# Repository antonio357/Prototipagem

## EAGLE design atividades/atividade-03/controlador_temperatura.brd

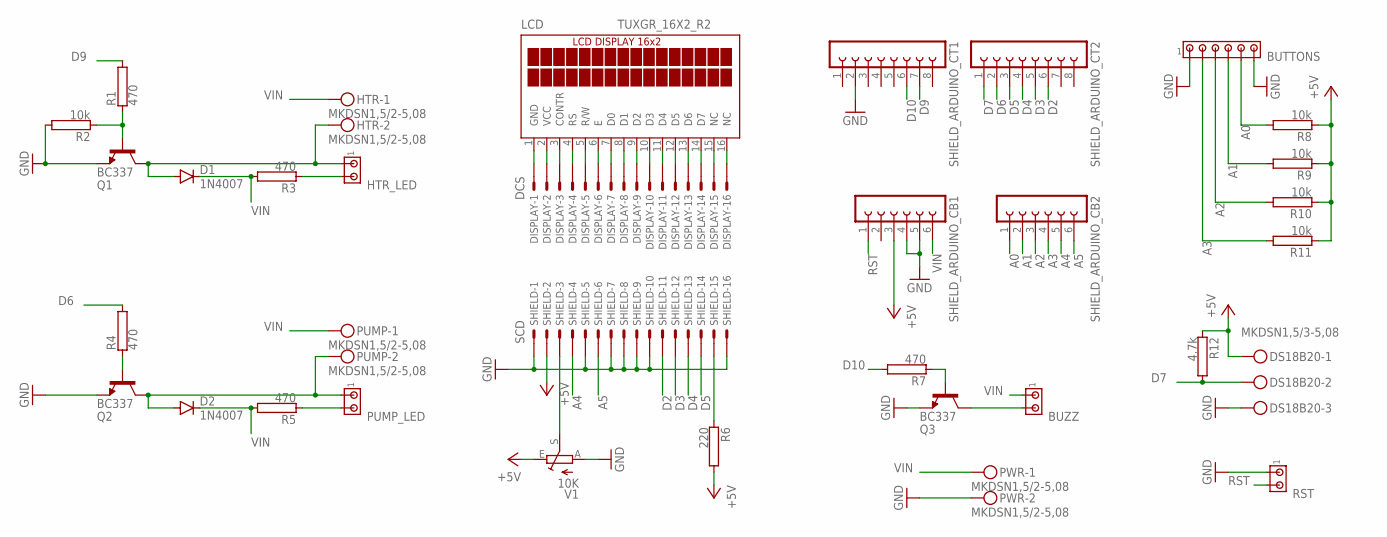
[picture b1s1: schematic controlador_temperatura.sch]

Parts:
BUTTONS: MTA06-100; 10X06MTA
BUZZ: MTA02-100; 10X02MTA
D1, D2: 1N4007; DO41-10
DISPLAY: DCS; 057-016-1
DS18B20: MKDSN1,5/3-5,08
HTR: MKDSN1,5/2-5,08
HTR_LED: MTA02-100; 10X02MTA
LCD: TUXGR_16X2_R2
PUMP: MKDSN1,5/2-5,08
PUMP_LED: MTA02-100; 10X02MTA
PWR: MKDSN1,5/2-5,08
Q1, Q2, Q3: BC337; TO92
R1, R3, R4, R5, R7: 470; RS1/8
R2, R8, R9, R10, R11: 10k; RS1/8
R6: 220; RS1/8
R12: 4.7k; RS1/8
RST: MTA02-100; 10X02MTA
SHIELD: SCD; 057-016-1
SHIELD_ARDUINO_CB1, SHIELD_ARDUINO_CB2: FE06-1; FE06
SHIELD_ARDUINO_CT1, SHIELD_ARDUINO_CT2: FE08-1; FE08
V1: 10K; B25P

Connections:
A0: BUTTONS.5, R8.2, SHIELD_ARDUINO_CB2.1
A1: BUTTONS.4, R9.2, SHIELD_ARDUINO_CB2.2
A2: BUTTONS.3, R10.2, SHIELD_ARDUINO_CB2.3
A3: BUTTONS.2, R11.2, SHIELD_ARDUINO_CB2.4
A4: SHIELD.4, SHIELD_ARDUINO_CB2.5
A5: SHIELD.6, SHIELD_ARDUINO_CB2.6
D2: SHIELD.11, SHIELD_ARDUINO_CT2.6
D3: SHIELD.12, SHIELD_ARDUINO_CT2.5
D4: SHIELD.13, SHIELD_ARDUINO_CT2.4
D5: SHIELD.14, SHIELD_ARDUINO_CT2.3
D6: R4.2, SHIELD_ARDUINO_CT2.2
D7: DS18B20.2, R12.2, SHIELD_ARDUINO_CT2.1
D9: R1.2, SHIELD_ARDUINO_CT1.7
D10: R7.2, SHIELD_ARDUINO_CT1.6
GND: BUTTONS.1, BUTTONS.6, DS18B20.3, PWR.2, Q1.1 (E), Q2.1 (E), Q3.1 (E), R2.2, RST.1, SHIELD.1, SHIELD.5, SHIELD.7, SHIELD.8, SHIELD.9, SHIELD.10, SHIELD.16, SHIELD_ARDUINO_CB1.4, SHIELD_ARDUINO_CB1.5, SHIELD_ARDUINO_CT1.2, V1.A
unnamed: Q1.2 (B), R1.1, R2.1
unnamed: Q2.2 (B), R4.1
unnamed: D1.A, HTR.2, HTR_LED.1, Q1.3 (C)
unnamed: D2.A, PUMP.2, PUMP_LED.1, Q2.3 (C)
unnamed: HTR_LED.2, R3.1
unnamed: PUMP_LED.2, R5.1
unnamed: DISPLAY.1, LCD.1 (GND)
unnamed: Q3.2 (B), R7.1
unnamed: BUZZ.2, Q3.3 (C)
unnamed: DISPLAY.2, LCD.2 (VCC)
unnamed: DISPLAY.3, LCD.3 (CONTR)
unnamed: DISPLAY.4, LCD.4 (RS)
unnamed: DISPLAY.5, LCD.5 (R/W)
unnamed: DISPLAY.6, LCD.6 (E)
unnamed: DISPLAY.7, LCD.7 (D0)
unnamed: DISPLAY.8, LCD.8 (D1)
unnamed: DISPLAY.9, LCD.9 (D2)
unnamed: DISPLAY.10, LCD.10 (D3)
unnamed: DISPLAY.11, LCD.11 (D4)
unnamed: DISPLAY.12, LCD.12 (D5)
unnamed: DISPLAY.13, LCD.13 (D6)
unnamed: DISPLAY.14, LCD.14 (D7)
unnamed: DISPLAY.15, LCD.15 (NC)
unnamed: DISPLAY.16, LCD.16 (NC)
unnamed: R6.1, SHIELD.15
unnamed: SHIELD.3, V1.S
RST: RST.2, SHIELD_ARDUINO_CB1.1
VCC: DS18B20.1, R6.2, R8.1, R9.1, R10.1, R11.1, R12.1, SHIELD.2, SHIELD_ARDUINO_CB1.3, V1.E
VIN: BUZZ.1, D1.C, D2.C, HTR.1, PUMP.1, PWR.1, R3.2, R5.2, SHIELD_ARDUINO_CB1.6

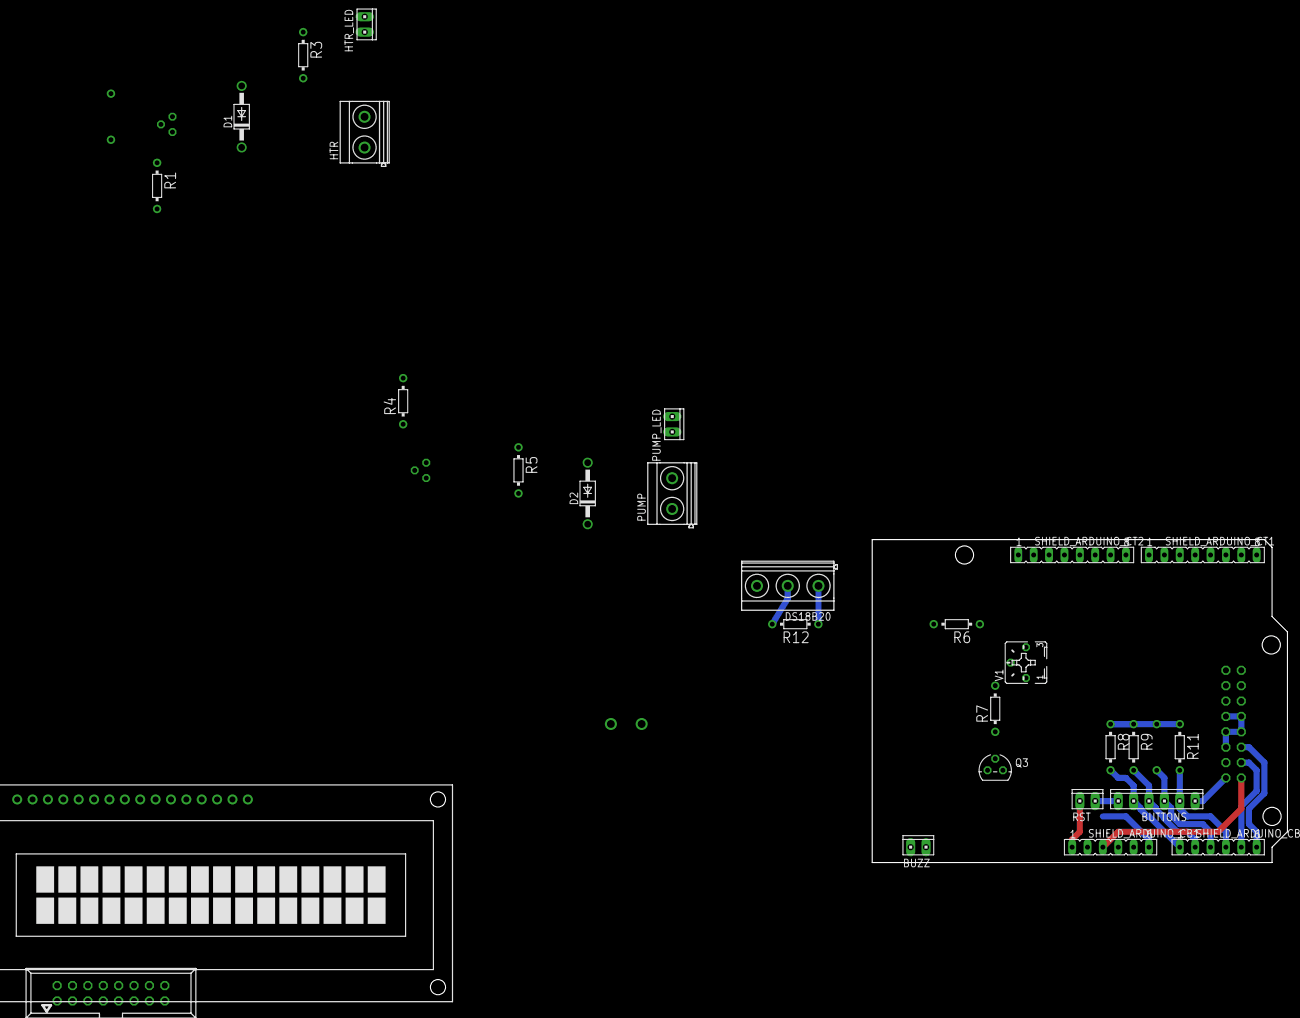
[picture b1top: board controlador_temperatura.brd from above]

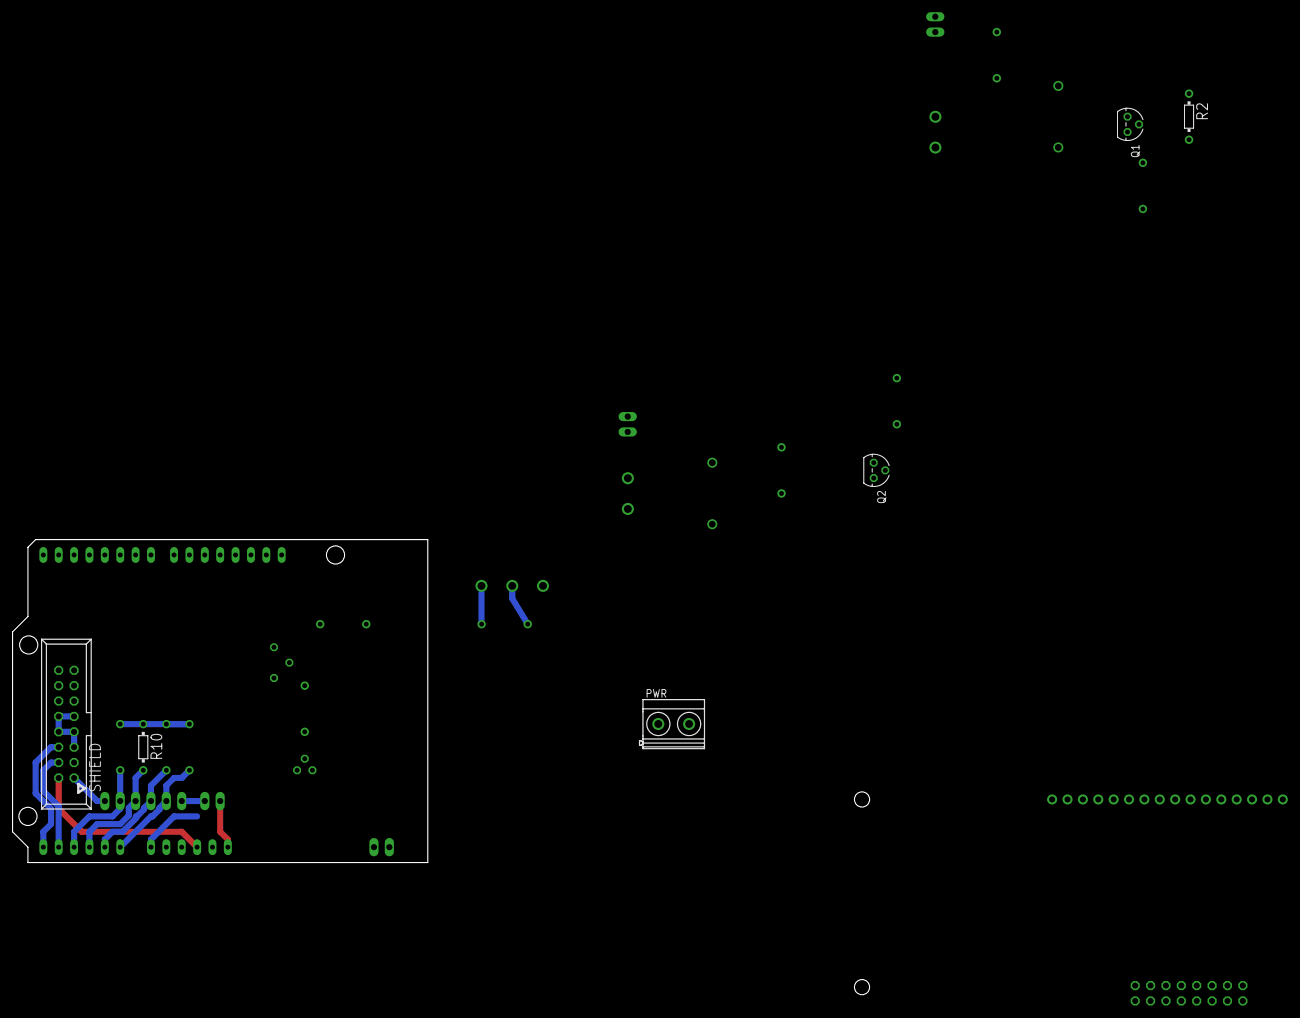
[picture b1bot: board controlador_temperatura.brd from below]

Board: 2 copper layers, 68.6 x 53.3 mm, 34 parts (6 on the bottom side), 44 nets.

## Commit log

2021-12-05 atividade 02, diagrama elétrico
2021-12-05 renomeando componentes
2021-12-19 heater scheme
2021-12-19 pump scheme
2021-12-19 pwr scheme
2021-12-19 display scheme
2021-12-19 ajustando valor do registor do display scheme
2021-12-19 buzzer scheme
2021-12-19 rst scheme
2021-12-19 buttons scheme
2021-12-19 oneWire buss cheme
2021-12-19 oneWire buss scheme label add
2021-12-19 buttons scheme labels add
2021-12-19 conectores shield arduino scheme
2021-12-19 display scheme corrigido
2021-12-19 organizando posições do schema
2021-12-19 abrindo circuito
2021-12-19 desenho do formato da placa
2021-12-19 posição dos furos da pcb
2021-12-19 posicionamento de alguns conectores
2021-12-19 agrupando os componentes
2021-12-19 buzz realinhado
2021-12-19 rst realinahdo
2021-12-19 power realinhado
2021-12-19 buttons realinhado
2021-12-19 conector do shield_display realinhado
2021-12-20 pump realinhado
2021-12-20 heater realinhado
2021-12-20 conectores de shield dentro da placa novamente
2021-12-20 check point
2021-12-20 checkpoint
2021-12-27 atividade 04
